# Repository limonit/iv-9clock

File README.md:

# iv-9clock
Clock based on iv-9 tubes and ATmega16

## What is it
This is clock based on iv-9 Numitron tubes. Repository contains .hex file for ATmega16 and complete schematic and PCB project designed in KiCad.
IV-9 are vacuum tubes that use filaments shaped into seven segment displays.

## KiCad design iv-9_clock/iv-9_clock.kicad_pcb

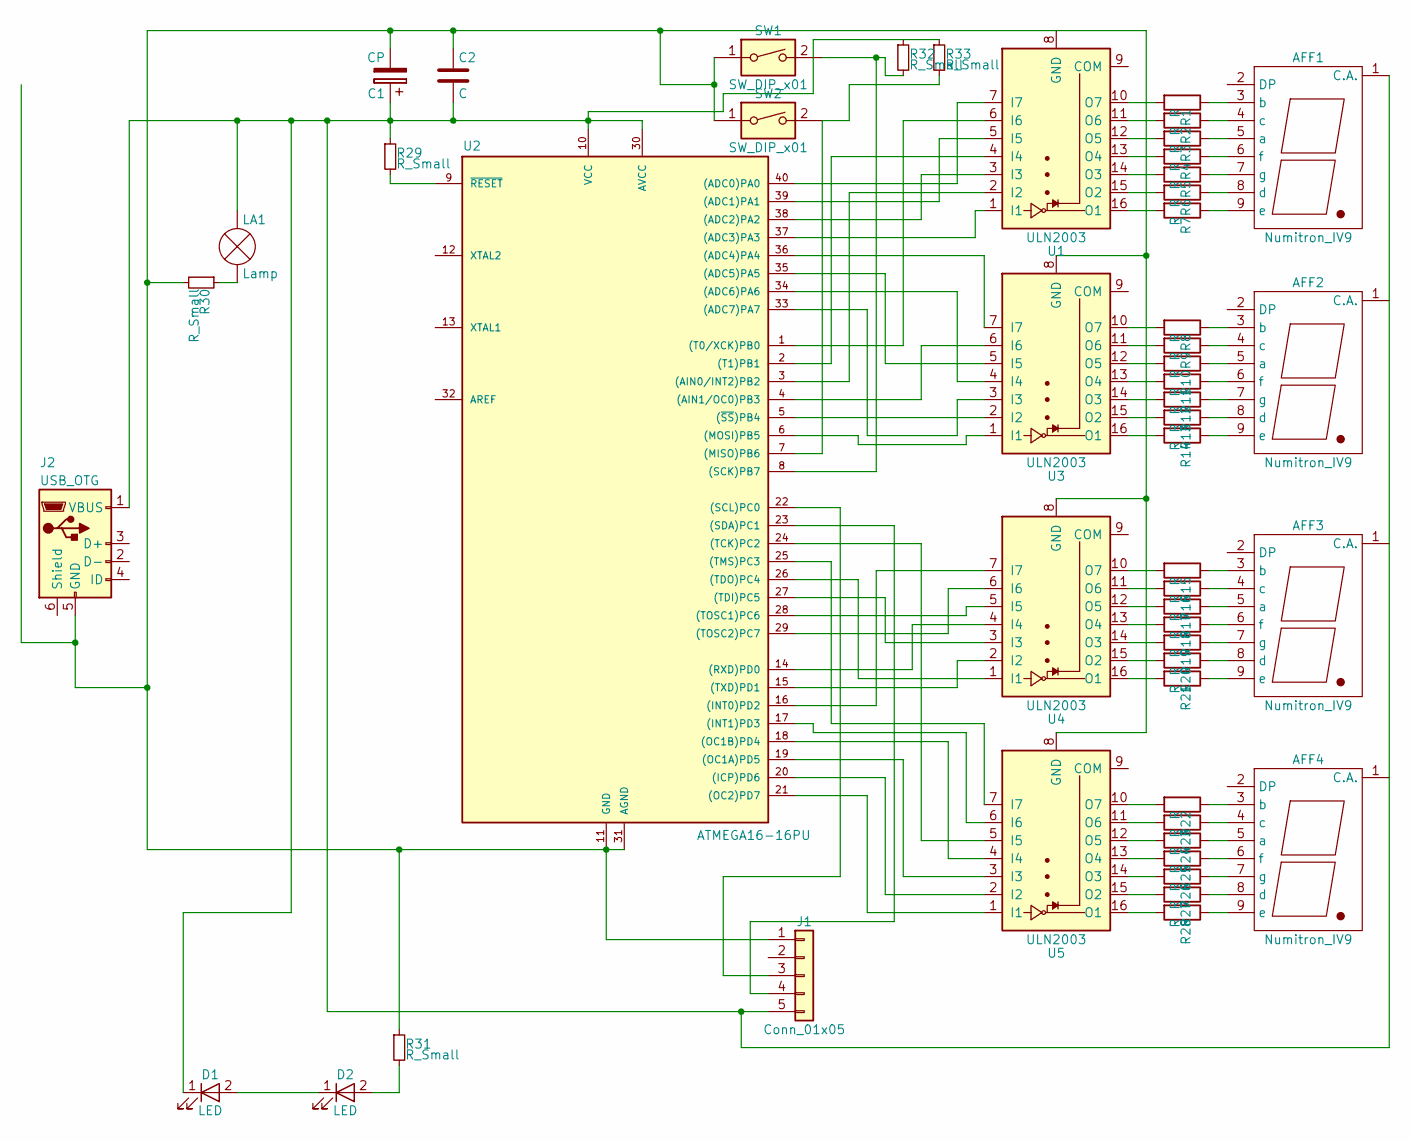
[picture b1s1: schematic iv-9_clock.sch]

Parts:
AFF1, AFF2, AFF3, AFF4: Numitron_IV9; NUM_IV-9
C1: CP; CP_Elec_10x10
C2: C; R_1206_HandSoldering
D1, D2: LED; LED_D4.0mm
J1: Conn_01x05; Pin_Header_Straight_1x05_Pitch2.54mm
J2: USB_OTG; Mini USB THT
LA1: Lamp; LED_D3.0mm_FlatTop
R1, R2, R3, R4, R5, R6, R7, R8, R9, R10, R11, R12, R13, R14, R15, R16, R17, R18, R19, R20, R21, R22, R23, R24, R25, R26, R27, R28: R; R_0805_HandSoldering
R29: R_Small; R_1206_HandSoldering
R30, R31, R32, R33: R_Small; R_0805_HandSoldering
SW1, SW2: SW_DIP_x01; SW_DIP_x1_W8.61mm_Slide_LowProfile
U1, U3, U4, U5: ULN2003; SOIC-16_3.9x9.9mm_Pitch1.27mm
U2: ATMEGA16-16PU; DIP-40_W15.24mm_Socket_LongPads

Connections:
unnamed: AFF1.1 (C.A.), C1.1, C2.2, D1.1 (K), J1.5, J2.1 (VBUS), LA1.2 (+), R29.1, R33.1, U2.10 (VCC), U2.30 (AVCC)
unnamed: AFF1.3 (b), R1.1
unnamed: AFF1.4 (c), R2.1
unnamed: AFF1.5 (a), R3.1
unnamed: AFF1.6 (f), R4.1
unnamed: AFF1.7 (g), R5.1
unnamed: AFF1.8 (d), R6.1
unnamed: AFF1.9 (e), R7.1
unnamed: AFF2.3 (b), R8.1
unnamed: AFF2.4 (c), R9.1
unnamed: AFF2.5 (a), R10.1
unnamed: AFF2.6 (f), R11.1
unnamed: AFF2.7 (g), R12.1
unnamed: AFF2.8 (d), R13.1
unnamed: AFF2.9 (e), R14.1
unnamed: AFF3.3 (b), R15.1
unnamed: AFF3.4 (c), R16.1
unnamed: AFF3.5 (a), R17.1
unnamed: AFF3.6 (f), R18.1
unnamed: AFF3.7 (g), R19.1
unnamed: AFF3.8 (d), R20.1
unnamed: AFF3.9 (e), R21.1
unnamed: AFF4.3 (b), R22.1
unnamed: AFF4.4 (c), R23.1
unnamed: AFF4.5 (a), R24.1
unnamed: AFF4.6 (f), R25.1
unnamed: AFF4.7 (g), R26.1
unnamed: AFF4.8 (d), R27.1
unnamed: AFF4.9 (e), R28.1
unnamed: C1.2, C2.1, J1.1, J2.5 (GND), R30.2, R31.1, SW1.1, SW2.1, U2.11 (GND), U2.31 (AGND), U3.8 (GND), U4.8 (GND), U5.8 (GND)
unnamed: D1.2 (A), D2.1 (K)
unnamed: D2.2 (A), R31.2
unnamed: J1.3, U2.22 ((SCL)PC0)
unnamed: J1.4, U2.23 ((SDA)PC1)
unnamed: LA1.1 (-), R30.1
unnamed: R1.2, U1.10 (O7)
unnamed: R2.2, U1.11 (O6)
unnamed: R3.2, U1.12 (O5)
unnamed: R4.2, U1.13 (O4)
unnamed: R5.2, U1.14 (O3)
unnamed: R6.2, U1.15 (O2)
unnamed: R7.2, U1.16 (O1)
unnamed: R8.2, U3.10 (O7)
unnamed: R9.2, U3.11 (O6)
unnamed: R10.2, U3.12 (O5)
unnamed: R11.2, U3.13 (O4)
unnamed: R12.2, U3.14 (O3)
unnamed: R13.2, U3.15 (O2)
unnamed: R14.2, U3.16 (O1)
unnamed: R15.2, U4.10 (O7)
unnamed: R16.2, U4.11 (O6)
unnamed: R17.2, U4.12 (O5)
unnamed: R18.2, U4.13 (O4)
unnamed: R19.2, U4.14 (O3)
unnamed: R20.2, U4.15 (O2)
unnamed: R21.2, U4.16 (O1)
unnamed: R22.2, U5.10 (O7)
unnamed: R23.2, U5.11 (O6)
unnamed: R24.2, U5.12 (O5)
unnamed: R25.2, U5.13 (O4)
unnamed: R26.2, U5.14 (O3)
unnamed: R27.2, U5.15 (O2)
unnamed: R28.2, U5.16 (O1)
unnamed: R29.2, U2.9 (~RESET)
unnamed: R32.2, SW1.2, U2.8 ((SCK)PB7)
unnamed: R33.2, SW2.2, U2.7 ((MISO)PB6)
unnamed: U1.1 (I1), U2.37 ((ADC3)PA3)
unnamed: U1.2 (I2), U2.3 ((AIN0/INT2)PB2)
unnamed: U1.3 (I3), U2.38 ((ADC2)PA2)
unnamed: U1.4 (I4), U2.2 ((T1)PB1)
unnamed: U1.5 (I5), U2.39 ((ADC1)PA1)
unnamed: U1.6 (I6), U2.1 ((T0/XCK)PB0)
unnamed: U1.7 (I7), U2.40 ((ADC0)PA0)
unnamed: U2.4 ((AIN1/OC0)PB3), U3.6 (I6)
unnamed: U2.5 ((~SS~)PB4), U3.2 (I2)
unnamed: U2.6 ((MOSI)PB5), U3.1 (I1)
unnamed: U2.14 ((RXD)PD0), U4.4 (I4)
unnamed: U2.15 ((TXD)PD1), U4.2 (I2)
unnamed: U2.16 ((INT0)PD2), U4.7 (I7)
unnamed: U2.17 ((INT1)PD3), U5.6 (I6)
unnamed: U2.18 ((OC1B)PD4), U5.4 (I4)
unnamed: U2.19 ((OC1A)PD5), U5.3 (I3)
unnamed: U2.20 ((ICP)PD6), U5.2 (I2)
unnamed: U2.21 ((OC2)PD7), U5.1 (I1)
unnamed: U2.24 ((TCK)PC2), U5.5 (I5)
unnamed: U2.25 ((TMS)PC3), U5.7 (I7)
unnamed: U2.26 ((TDO)PC4), U4.1 (I1)
unnamed: U2.27 ((TDI)PC5), U4.3 (I3)
unnamed: U2.28 ((TOSC1)PC6), U4.5 (I5)
unnamed: U2.29 ((TOSC2)PC7), U4.6 (I6)
unnamed: U2.33 ((ADC7)PA7), U3.3 (I3)
unnamed: U2.34 ((ADC6)PA6), U3.4 (I4)
unnamed: U2.35 ((ADC5)PA5), U3.5 (I5)
unnamed: U2.36 ((ADC4)PA4), U3.7 (I7)

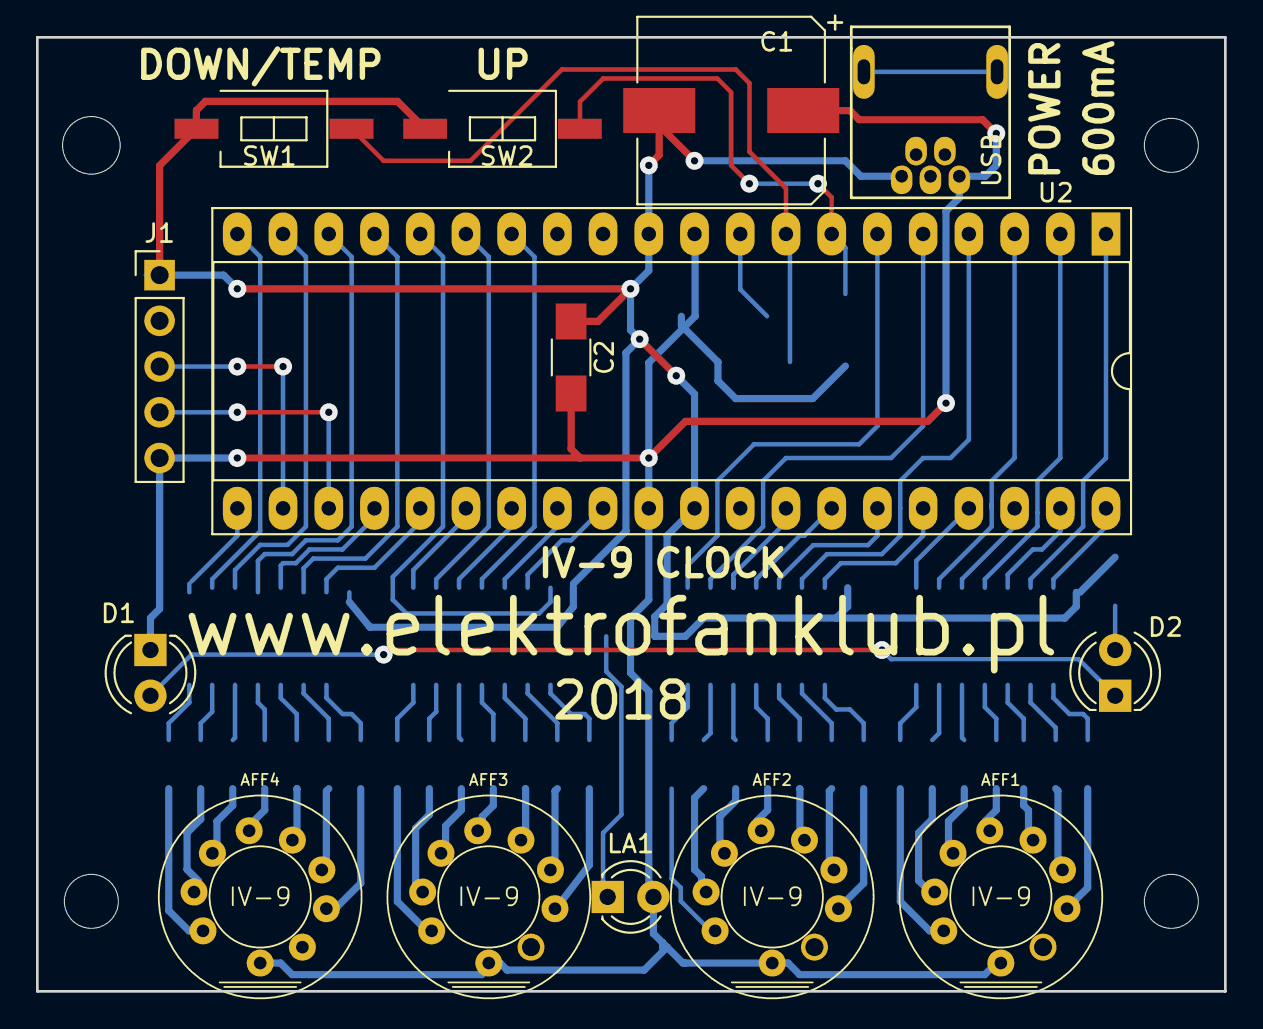
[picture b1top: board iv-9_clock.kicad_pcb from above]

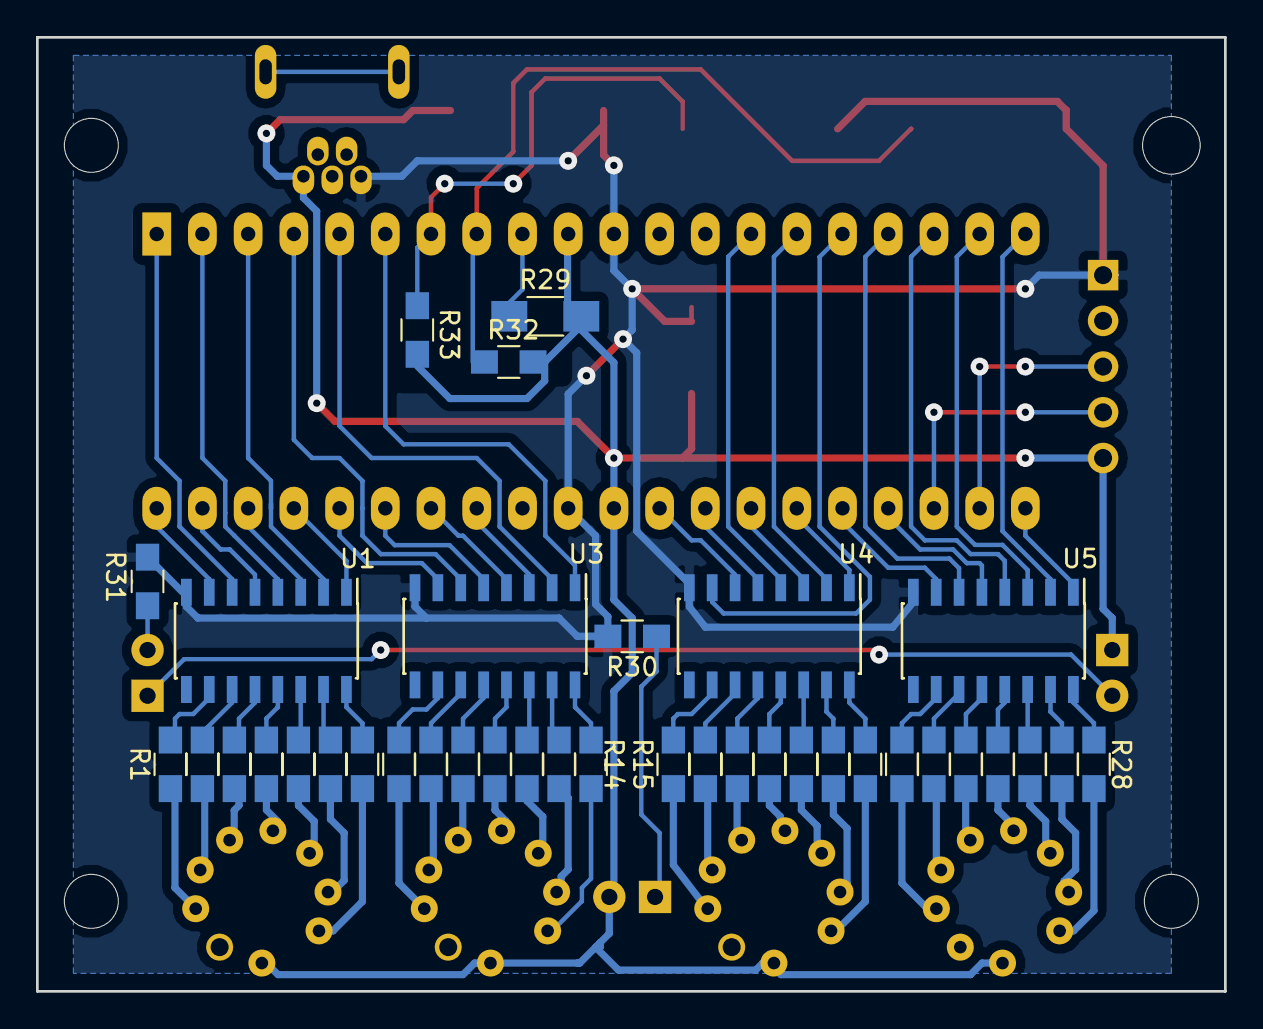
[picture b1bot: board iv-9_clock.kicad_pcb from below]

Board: 2 copper layers, 66.0 x 53.0 mm, 51 parts (37 on the bottom side), 94 nets.

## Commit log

2020-01-30 Initial
2020-01-30 Image added
2020-01-30 Image update
